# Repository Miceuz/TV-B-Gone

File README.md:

TV-B-Gone
=========

This is my custom TV-be-gone implementation. The board was ment to fit on a standard double AA battery compartment. In general, this design was driven by what parts do I have available in my junk box, thus I've chosen Attiny44  as main microcontroller as I have plenty of them. Leds are driven by mosfets because I had some scavenged from some motherboard.

The code is from Adafruit - https://github.com/adafruit/TV-B-Gone-kit. I've removed all the codes for North American TVs and commented out the biggest codes for European TVs as Attiny44 does not have enough flash to fit them all. I've inverted PWM because I'm driving LEDs via N-channel mosfets, unlike BJTs in Adafruit version.

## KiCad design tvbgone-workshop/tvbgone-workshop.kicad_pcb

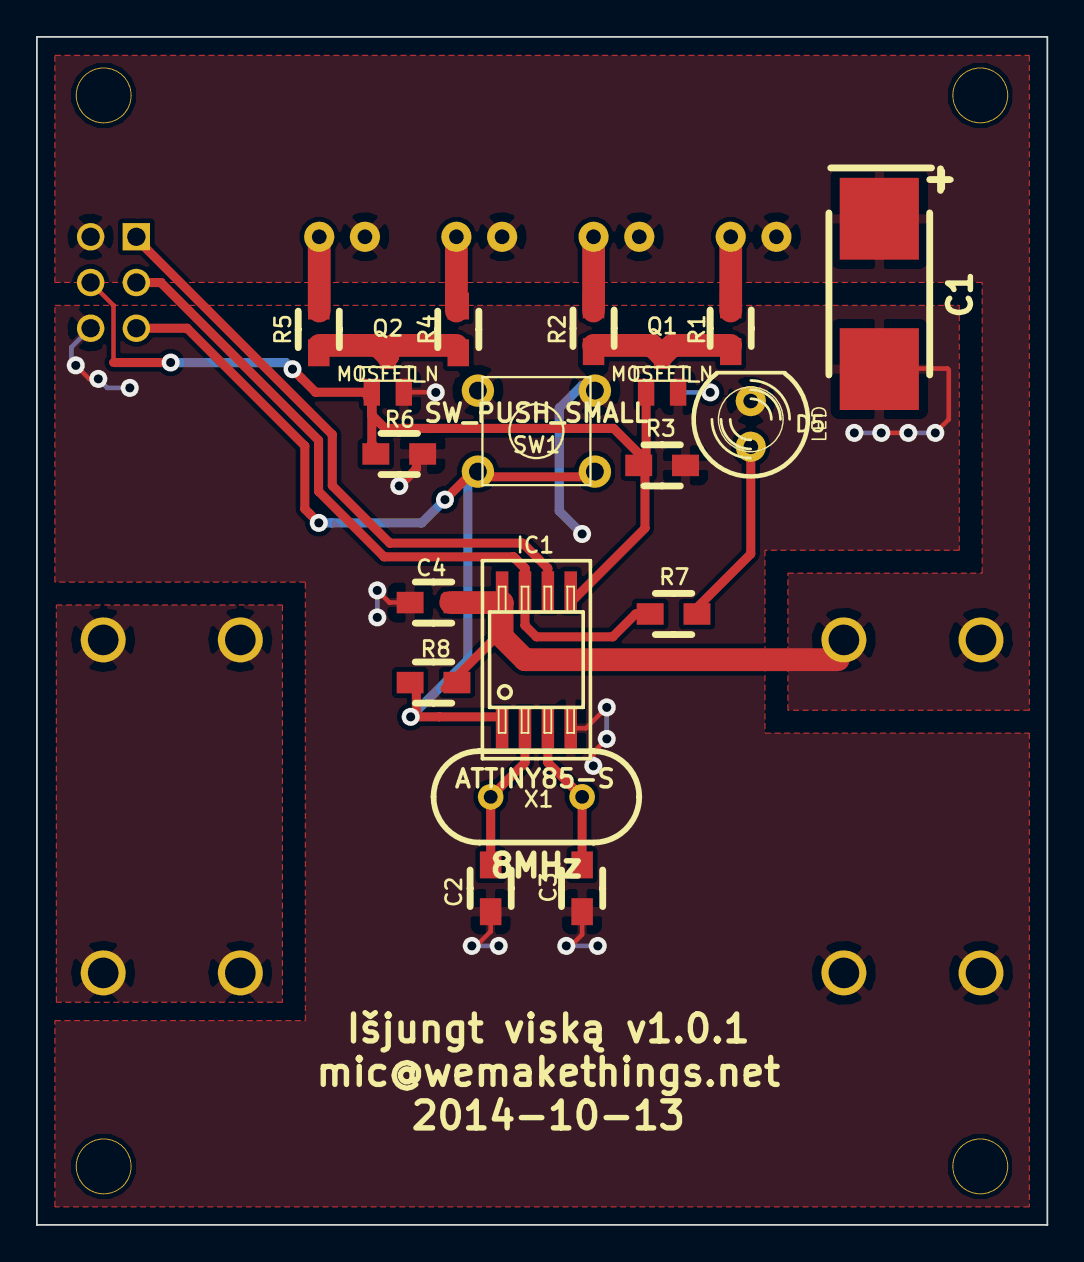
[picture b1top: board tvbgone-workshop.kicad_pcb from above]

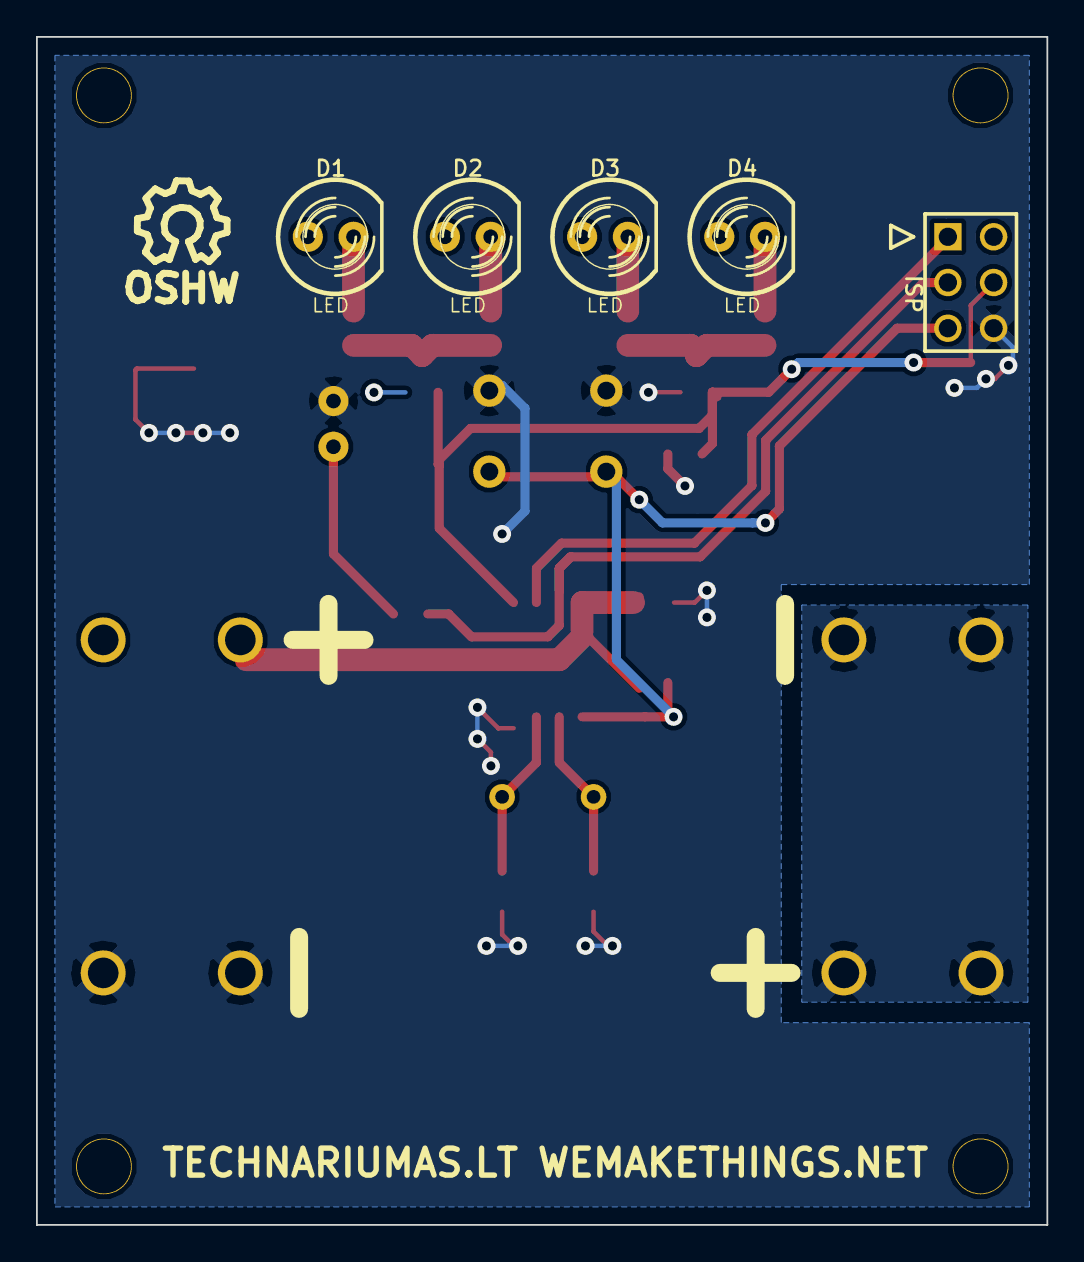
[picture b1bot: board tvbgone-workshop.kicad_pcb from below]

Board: 2 copper layers, 56.1 x 66.0 mm, 26 parts (8 on the bottom side), 16 nets.

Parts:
BT1: BATTERY; BATT-AA-BK92
BT2: BATTERY; BATT-AA-BK92-bold
C1: CAPAPOL; TantalC_SizeE_EIA-7360_HandSoldering
C2, C3: 22p; Resistor_SMD0805_HandSoldering
C4: 100n; Resistor_SMD0805_HandSoldering
D1, D2, D3, D4, D5: LED; LED-5MM
IC1: ATTINY85-S; SO8_200mil_wide
ISP: AVR-ISP-6; pin_array_3x2
Q1, Q2: MOSFET_N; SOT23GDS
R1, R2, R3, R4, R5, R6, R8: 10k; Resistor_SMD0805_HandSoldering
R7: 330; Resistor_SMD0805_HandSoldering
SW1: SW_PUSH_SMALL
SYM: Symbol_OSHW-Logo_SilkScreen_07Jul2012; Symbol_OSHW-Logo_SilkScreen
X1: 8MHz; HC-49V

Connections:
/MISO: IC1.6, ISP.1
/MOSI: IC1.5, ISP.4, Q1.G, Q2.G, R3.1, R6.1
/RESET: IC1.1, ISP.5, R8.1, SW1.1
/SCK: IC1.7, ISP.3, R7.2
GND: BT2.2, C1.2, C2.2, C3.2, C4.2, D5.2, IC1.4, ISP.6, Q1.S, Q2.S, R3.2, R6.2, SW1.2
unnamed: Q1.D, R1.2, R2.2
unnamed: Q2.D, R4.2, R5.2
unnamed: C3.1, IC1.3, X1.2
unnamed: C2.1, IC1.2, X1.1
unnamed: D5.1, R7.1
unnamed: BT1.2, BT2.1
unnamed: D3.2, R4.1
unnamed: D1.2, R1.1
unnamed: D2.2, R2.1
unnamed: D4.2, R5.1
VCC: BT1.1, C1.1, C4.1, D1.1, D2.1, D3.1, D4.1, IC1.8, ISP.2, R8.2

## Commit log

2013-01-13 readme
2013-01-21 + attiny85 version
2013-01-21 some more fixes
2014-03-02 working on a kit for a workshop, some alpha board and BOM
2014-03-29 latest changes
2014-03-30 add holes, changes size of the board a bit, shuffle stuf around
2014-03-30 add gerbers
2014-05-19 opit
2014-05-20 changed orientation of the board, distances to holes according to case drawings
2014-05-20 more documentation
2014-05-22 changed MCU package, a bit more silkscreen markings for batteries and a polar cap
2014-05-22 move to the new kicad, play around with 3d packages, make pads bigger for easier soldering
2014-12-17 some leftovers
2014-12-17 add the latest gerbers
2014-12-17 add logo and a 3d render
2014-12-17 cleanup
2014-12-17 copy and slightly modify firmware from Adafruit
